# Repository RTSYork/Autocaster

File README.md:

The Autocaster
==============
### An FPGA-Based Embedded System to Autonomously Play Music Video Games
#### Russell Joyce, Department of Computer Science, University of York, UK
For more information, see https://wiki.york.ac.uk/display/RTS/The+Autocaster

---

The included 'download.bit' file is ready for configuring the FPGA using Xilinx iMPACT or Digilent Adept software. The .bit file includes the compiled MicroBlaze software .elf file.

#### Requirements for building:
- Xilinx ISE Design Tools 14.3 (Embedded or System Edition)
- Arduino 1.0.4 (http://www.arduino.cc/en/Main/Software)
- Teensyduino 1.13 (http://www.pjrc.com/teensy/td_download.html)
- Microsoft Visual Studio 2010 (for optional support programs)

---

Xilinx EDK Project
-------------------
- Open 'GH-EDK\system.xmp' in Xilinx Platform Studio
- Use 'Generate Bitstream' command to create a .bit file or 'Export to SDK' to generate .bit file and open SDK project

Xilinx SDK Project
-------------------
- In Xilinx SDK import project and choose 'GH-SDK' folder
- Import all three projects
- Use 'Export to SDK' command in XPS and select the workspace to copy over .bit file, etc.
- Use 'Program FPGA' and run as 'Execute on Hardware' to run project

Teensyduino Project
-------------------
- Copy the contents of the 'Teensy/teensy' folder to the 'hardware/teensy' folder in the Arduino install directory
- Open 'Guitar/Guitar.ino' in Arduino IDE
- From tools menu, select "Teensy 3.0" as the board
- From tools menu, select "My Guitar" as the USB Type
- Use 'Verify' or 'Upload' to build the program
- Press the reset button on the Teensy board to program

UART Image Capture
-------------------
- Open 'UARTImage/UARTImage.sln' in Microsoft Visual Studio

Image Filter Test
-------------------
- Open 'Image Filter/Image Filter.sln' in Microsoft Visual Studio

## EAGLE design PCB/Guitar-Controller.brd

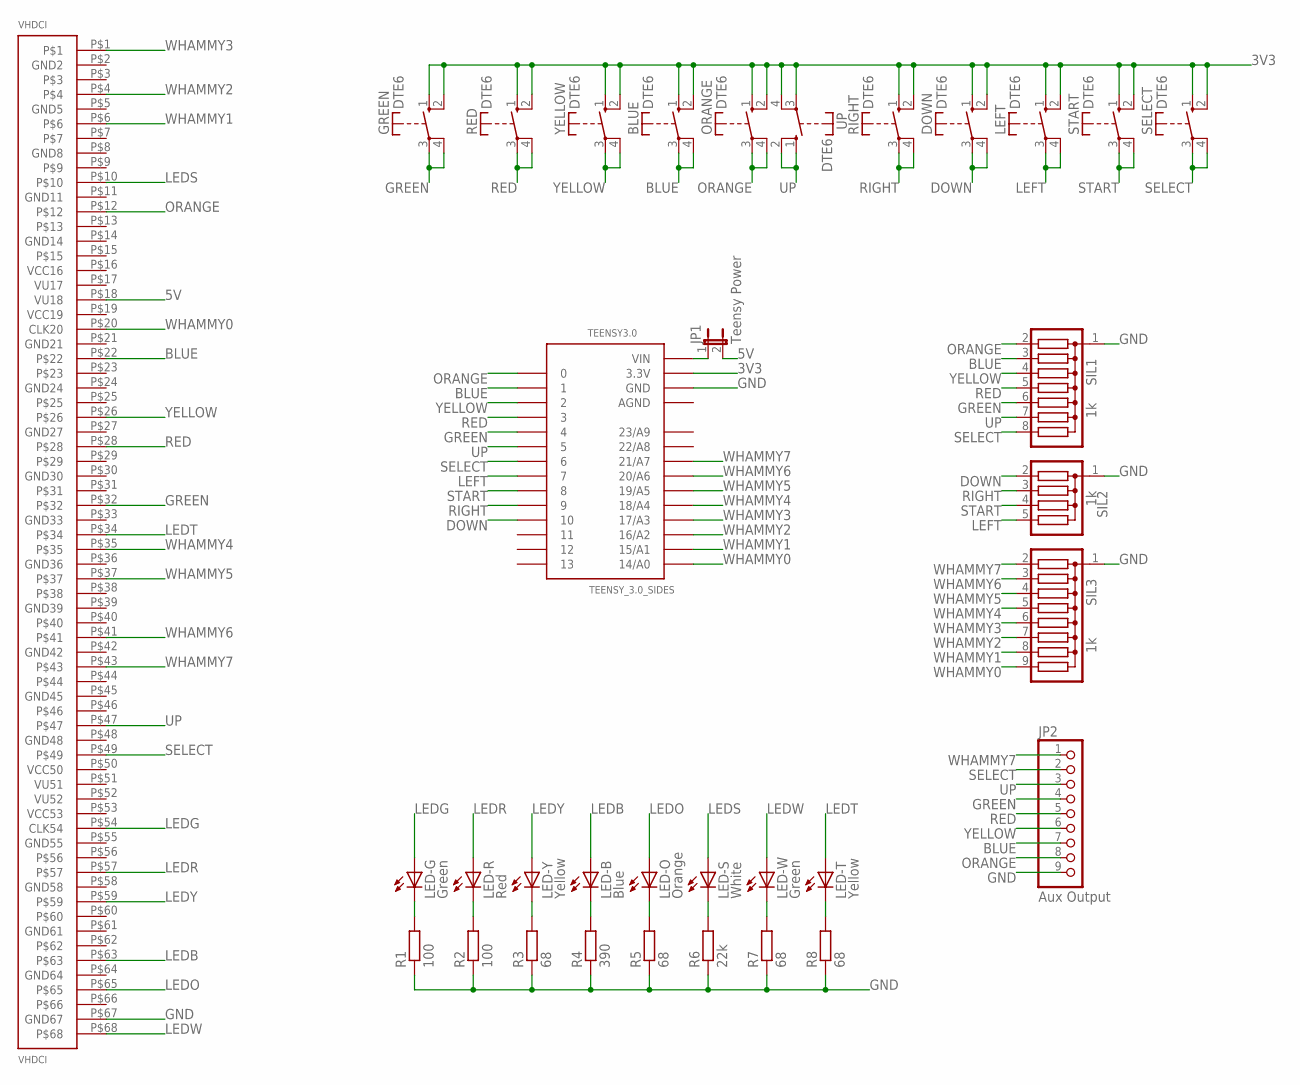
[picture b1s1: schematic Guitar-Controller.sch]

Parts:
BLUE: DTE6
DOWN: DTE6
GREEN: DTE6
JP1: Teensy Power; JP1
JP2: Aux Output; 1X09/90
LED-B: Blue; LED2X5
LED-G: Green; LED2X5
LED-O: Orange; LED2X5
LED-R: Red; LED2X5
LED-S: White; LED5MM
LED-T: Yellow; LED3MM
LED-W: Green; LED3MM
LED-Y: Yellow; LED2X5
LEFT: DTE6
ORANGE: DTE6
R1, R2: 100; R0805
R3, R5, R7, R8: 68; R0805
R4: 390; R0805
R6: 22k; R0805
RED: DTE6
RIGHT: DTE6
SELECT: DTE6
SIL1: 1k; SIL8
SIL2: 1k; SIL5
SIL3: 1k; SIL9
START: DTE6
TEENSY3.0: TEENSY_3.0_SIDES
UP: DTE6
VHDCI: VHDCI-PLUG; R-HI-008068-2
YELLOW: DTE6

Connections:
3V3: BLUE.1 (S), BLUE.2 (S), DOWN.1 (S), DOWN.2 (S), GREEN.1 (S), GREEN.2 (S), LEFT.1 (S), LEFT.2 (S), ORANGE.1 (S), ORANGE.2 (S), RED.1 (S), RED.2 (S), RIGHT.1 (S), RIGHT.2 (S), SELECT.1 (S), SELECT.2 (S), START.1 (S), START.2 (S), TEENSY3.0.3.3V, UP.3, UP.4, YELLOW.1 (S), YELLOW.2 (S)
5V: JP1.2, VHDCI.P$18 (VU18)
AGND: TEENSY3.0.AGND
BLUE: BLUE.3, BLUE.4, JP2.7, SIL1.3, TEENSY3.0.1, VHDCI.P$22
DOWN: DOWN.3, DOWN.4, SIL2.2, TEENSY3.0.10
GND: JP2.9, R1.1, R2.1, R3.1, R4.1, R5.1, R6.1, R7.1, R8.1, SIL1.1, SIL2.1, SIL3.1, TEENSY3.0.GND, VHDCI.P$67 (GND67)
GREEN: GREEN.3, GREEN.4, JP2.4, SIL1.6, TEENSY3.0.4, VHDCI.P$32
LEDB: LED-B.A, VHDCI.P$63
LEDG: LED-G.A, VHDCI.P$54 (CLK54)
LEDO: LED-O.A, VHDCI.P$65
LEDR: LED-R.A, VHDCI.P$57
LEDS: LED-S.A, VHDCI.P$10
LEDT: LED-T.A, VHDCI.P$34
LEDW: LED-W.A, VHDCI.P$68
LEDY: LED-Y.A, VHDCI.P$59
LEFT: LEFT.3, LEFT.4, SIL2.5, TEENSY3.0.7
unnamed: LED-R.K (C), R2.2
unnamed: LED-G.K (C), R1.2
unnamed: LED-Y.K (C), R3.2
unnamed: LED-B.K (C), R4.2
unnamed: LED-O.K (C), R5.2
unnamed: LED-S.K (C), R6.2
unnamed: LED-W.K (C), R7.2
unnamed: LED-T.K (C), R8.2
unnamed: JP1.1, TEENSY3.0.VIN
ORANGE: JP2.8, ORANGE.3, ORANGE.4, SIL1.2, TEENSY3.0.0, VHDCI.P$12
RED: JP2.5, RED.3, RED.4, SIL1.5, TEENSY3.0.3, VHDCI.P$28
RIGHT: RIGHT.3, RIGHT.4, SIL2.3, TEENSY3.0.9
SELECT: JP2.2, SELECT.3, SELECT.4, SIL1.8, TEENSY3.0.6, VHDCI.P$49
START: SIL2.4, START.3, START.4, TEENSY3.0.8
UP: JP2.3, SIL1.7, TEENSY3.0.5, UP.1 (S), UP.2 (S), VHDCI.P$47
WHAMMY0: SIL3.9, TEENSY3.0.14/A0, VHDCI.P$20 (CLK20)
WHAMMY1: SIL3.8, TEENSY3.0.15/A1, VHDCI.P$6
WHAMMY2: SIL3.7, TEENSY3.0.16/A2, VHDCI.P$4
WHAMMY3: SIL3.6, TEENSY3.0.17/A3, VHDCI.P$1
WHAMMY4: SIL3.5, TEENSY3.0.18/A4, VHDCI.P$35
WHAMMY5: SIL3.4, TEENSY3.0.19/A5, VHDCI.P$37
WHAMMY6: SIL3.3, TEENSY3.0.20/A6, VHDCI.P$41
WHAMMY7: JP2.1, SIL3.2, TEENSY3.0.21/A7, VHDCI.P$43
YELLOW: JP2.6, SIL1.4, TEENSY3.0.2, VHDCI.P$26, YELLOW.3, YELLOW.4

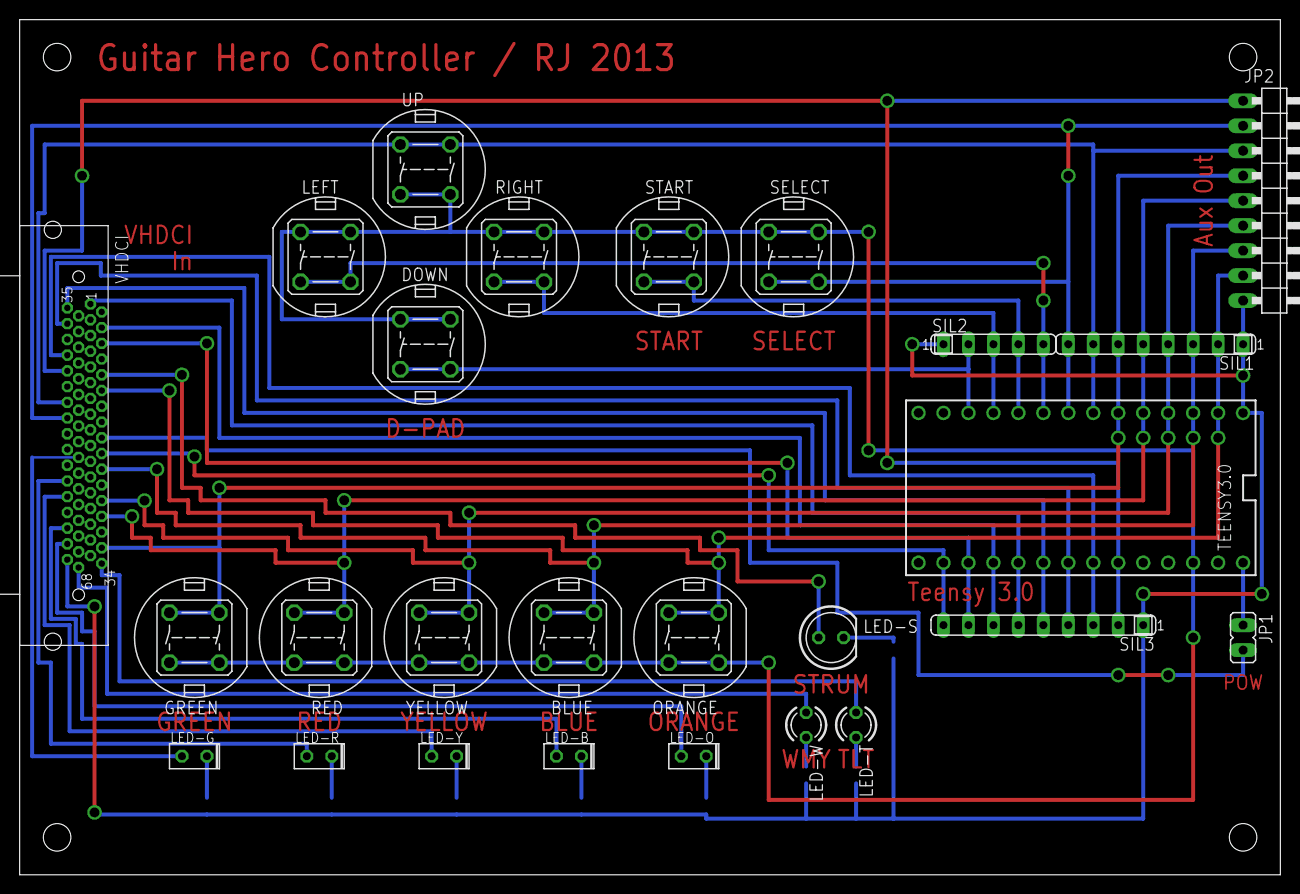
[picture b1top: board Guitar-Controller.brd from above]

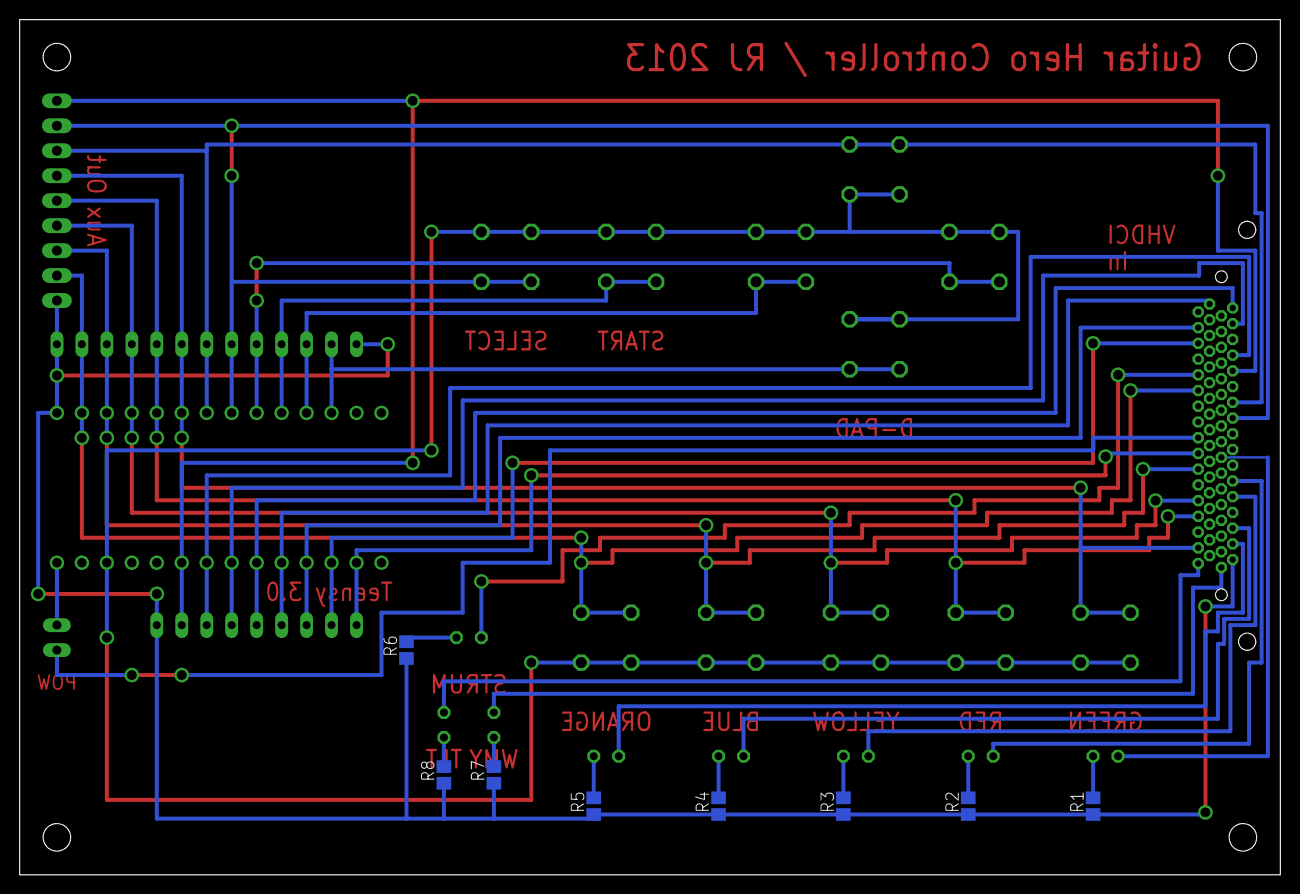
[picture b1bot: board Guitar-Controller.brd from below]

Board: 2 copper layers, 128.2 x 87.0 mm, 34 parts (8 on the bottom side), 39 nets.

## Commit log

2013-02-06 Added report template
2013-03-24 Moved gitignore LaTeX rules to Report folder
2013-03-24 Added UARTImage project
2013-03-24 Added Image Filter project
2013-03-24 Added EDK project
2013-03-24 Added Xilinx SDK project
2013-03-24 Moved disk
2013-03-24 Updated global .gitignore for NTFS on OS X
2013-03-25 Added .gitattributes
2013-03-25 Moved to Windows
    Normalised line endings, etc.
2013-03-25 Updated Image Filter
2013-03-25 Image Filter: Removed colour difference threshold
2013-03-25 EDK: Added lock file to .gitignore
2013-03-25 EDK: Connected image_filter_0 ACLK
2013-03-26 EDK: Removed generated HDL
2013-03-26 EDK: Removed generated platgen options
2013-03-26 EDK: Added Bluespec files for gh_player core
2013-03-26 EDK: Added GUI files to .gitignore
2013-03-26 EDK: Added Greyscale and Threshold image filters
2013-03-28 EDK: Added enables to image filters
2013-03-28 EDK: Changed the way greyscale is calculated
2013-03-28 EDK: Renamed filter enables in image_filter
2013-03-28 SDK: Updated hardware description
2013-03-28 SDK: Added switch control of image_filter enables
2013-03-28 Image Filter: Changed greyscale and threshold
2013-03-28 EDK: Changed image_filter first threshold value
2013-03-28 EDK: Added C driver for image_filter
2013-03-28 SDK: Project update
2013-03-28 SDK: Implemented image_filter driver
2013-03-29 Updated for OS X permissions
2013-03-29 EDK: Added binary out to image_filter threshold
2013-03-30 EDK: Updated image_filter filter connections
2013-03-30 EDK: Removed gry_out from image_filter Threshold
2013-03-30 EDK: Changed image_filter mix output
2013-03-31 EDK: Added Blur, Edge and Mix to image_filter
2013-03-31 Image Filter: Updated filters to match hardware
2013-03-31 EDK: Added register for image_filter threshold
2013-03-31 SDK: Updated image_filter driver & implementation
2013-03-31 EDK: Tidied up 'user_logic.v' files
2013-04-01 SDK: Updated gh_player driver
    Added old/new player type selection
2013-04-01 SDK: gh_player type implementation & LED changes
    - Implemented changes from gh_player driver
    - Added LED status to filter display type
2013-04-01 EDK: Added player_filtered Verilog module
2013-04-01 EDK: Initial player_filtered implementation
2013-04-01 SDK: Updated fret detector positions
2013-04-01 Image Filter: Updated fret detector positions
2013-04-01 SDK: Switched to using filtered player hardware
2013-04-02 SDK: Added extra switch to control filters
2013-04-02 EDK: Changed some regs to wires in Blur filter
2013-04-02 EDK: Changed some regs to wires in Edge filter
2013-04-02 Updated gitignores
2013-04-04 EDK: Removed previous row in blur for test
2013-04-04 EDK: Removed lastrow from Edge filter to test
2013-04-04 EDK: Added Chipscope to image_filter AXIS to test
2013-04-04 Teensy: Initial code commit (out of date)
2013-04-06 EDK: Added delay to old player
2013-04-06 SDK: Added delay register to gh_player driver
2013-04-06 EDK: Added delay to image_filter AXIS controls
2013-04-15 Teensy: Updated files
2013-04-15 EDK: Removed Chipscope probes
2013-04-15 EDK Removed Chipscope probes
2013-04-15 MB: Changes to work with delay player system
    - Changed buttons to delay
    - Changed offsets
    - Changed thresholds
2013-04-15 EDK: Changed Fret to use 1 point instead of 3
2013-04-15 EDK: Changed to Blur and Edge filters
    - Re-implemented filters
    - Changed to using vectors
2013-04-15 EDK: Fixed filter Hsync (potentially)
2013-04-15 EDK: Removed filter AXIS signal delays
2013-04-15 EDK: Added delay to filtered player
2013-04-16 MB: Changed thresholds for delayed detection
2013-04-16 Teensy: Updated code
    - Tidied up
    - Shortened delay
2013-04-16 MB: Increased fret delay and offsets
2013-04-16 Teensy: Changed delay back to 200ms
2013-04-16 EDK: Possible blur filter fixes
2013-04-16 EDK: Work on filtered fret detector
2013-04-16 EDK: Possible filter AXIS timing fixes
2013-04-17 EDK: Changes to Fret detector
2013-04-17 EDK: Changes to Filtered Fret detector
2013-04-17 EDK: Fix to filter user_logic
2013-04-17 EDK: Image Filter fixes
2013-04-17 EDK: Fret detector changes
2013-04-17 EDK: Allow selection of processing image filter
2013-04-17 MB: Threshold changes
2013-04-19 EDK: Updated player to use Strum module & removed smoothing code
2013-04-24 EDK: Increased MicroBlaze block RAM
2013-04-24 EDK/SDK: Image filter changes
2013-04-24 EDK: Fret changes
2013-04-24 SDK: Type/delay Changes
2013-04-24 EDK: Made Fret detection zone narrower
2013-05-04 EDK: Made Digilent cores local
2013-05-04 Added final bit-file
2013-05-06 Added code readme
2013-06-25 Updated ReadMe with build information
2013-08-12 Teensy: Updated input pins ready for new PCB
    Removed pins that aren't actually used
2013-08-13 PCB: Added initial PCB schematic and board design Includes Eagle libraries for VHDCI and Teensy
2013-08-13 PCB: Moved pin labels on VHDCI off top layer
2013-08-13 PCB: Changed all pin connections to use bottom layer
2013-08-13 PCB: Final PCB changes (hopefully)
2013-08-13 EDK: Updated XPS project to version 14.6
2013-08-13 EDK: Added option to use two threads for synthesis On 'par' and 'map' stages
2013-08-13 EDK: Added Ethernet core to design
2013-08-14 Fixed timing errors in Image Filter core
2013-08-14 SDK: Updated SDK project for 14.6 + Ethernet core
2013-08-15 SDK: Added Ethernet init and UDP send functions Currently not used in main loop
2013-08-15 Added EthernetImage C# program Allows image capture over Ethernet (similar to UART program)
2013-08-15 SDK: Implemented Ethernet screenshot transmission Replaces UART method for now
2013-08-15 SDK: Added position and thresholds gor Guitar Hero
2013-08-15 SDK: Changed SW3 to output status over UART
2013-08-20 PCB: Fixed errors on VHDC connector and changed SILs SIL change is to work with what is available in department
2013-08-20 PCB: Updated VHDCI connector to match FPGA pins
2013-08-20 EDK: Updated UCF for new output pins to PCB
2013-08-20 EDK: Changed Blur and Edge filters to use subframe Fixes timing errors by only applying filter to portion of image
2013-08-21 Updated Teensy pins to match new PCB layout
2013-08-21 SDK: Added definition to swtich between games
2013-08-21 Added EthernetStream C# program For receiving video streamed from the Atlys over Ethernet
2013-08-21 SDK: Improved Ethernet functions Added check for hardware to be free and send with pre-added payload
2013-08-21 SDK: Added video sending over Ethernet Includes changes to VDMA interrupt handling
2013-08-22 SDK: Added options header for game/filter choice
2013-08-22 EDK: Updated Fret detector module To work better with whammy - now looks at a cross of pixels
2013-08-22 SDK: Changed overlay crosses to match Fret module
2013-08-22 SDK: Added line numbers to Ethernet video stream Includes updates to EthernetStream receiver program
2013-08-23 SDK: Minor changes to cross drawing function
2013-08-23 EDK: Updated Fret module vertical detection
2013-08-23 EDK: Changed Strum module to increase strum speed Now checks for fret differences, currently strums too often in some cases
2013-08-23 SDK: Changed RB fret thresholds for new hardware
2013-08-28 SDK: Fixed options header for multiple includes Fixes delay initial value bug
2013-08-28 SDK: Changed Ethernet remote address to broadcast Broadcast subnet is RTS lab vLAN
2013-08-28 SDK: Reversed button directions for delay change
2013-08-28 EthernetImage: Updated to work with frame stream
2013-08-28 SDK: Updated frame stream capture to use Ethernet
2013-08-28 EDK: Updated fret module for smaller vertical area
2013-08-28 EDK: Changed strum module back to slower reaction Prevents over-strumming on some notes
2013-08-28 EthernetImage: Increased UDPClient buffer size Still has some issues with packet dropping - might be MicroBlaze side
2013-08-28 SDK: Tuned player delay, thresholds and positions Still has some problems, mostly caused by interference from sparks
2013-08-29 EDK: Tidied up unused bits of Fret module
2013-08-29 EDK: Strum module now looks for fret differences Not yet fully tested
2013-08-29 EthernetImage: Added status text for each frame
2013-08-29 SDK: Outputs status messages with image frames
2013-08-29 SDK: Further tuning of positions and thresholds Now works above sparks. Good except for glitch with yellow sustained notes
2013-08-29 SDK: Changed crosses on screen to detector markers I.e. now in the same shape as the detectors
2013-08-30 EDK: Added tilt enable and fret override to player Allows MB to control fret outputs (for navigation, etc)
2013-08-30 EDK: Updated gh_player driver for new options
2013-08-30 SDK: Added option to enable/disable tilt
2013-08-30 SDK: Increased stack and heap sizes Just in case...
2013-08-30 SDK: Moved more global defines into options.h Includes change in RB delay
2013-08-30 SDK: Further threshold tuning Mostly fixes yellow issue (delay 10 helps too), improves very rapid notes
2013-09-02 EDK: Added screen_detector IP core Looks for certain features on screen. Currently set up for RB3 song end.
2013-09-02 SDK: Added screen_detector driver
2013-09-03 SDK: Renamed VDMA interrupts to clarify their use
2013-09-03 EDK: Updated screen detector code
2013-09-05 EDK: Added additional screen detectors
2013-09-05 SDK: Limited Ethernet MAC address To stop it breaking the network with too many broadcast packets
2013-09-05 SDK: Changed center button to reset VDMA
2013-09-05 SDK: Added auto song progression and player enable Based around screen detector core. Also outputs status over Ethernet.
2013-09-05 SDK: Tidied up a lot of code/debug messages UART output now shows actions of initialisation and each switch
2013-09-05 EthernetStream: Added text console output Shows current system state, as sent over Ethernet
2013-09-05 Added flash and programming bitfiles
2015-04-13 Removed Xilinx copyright notice from 'main.c'
2015-06-27 Fix in readme
2017-07-03 Updated URL in readme
